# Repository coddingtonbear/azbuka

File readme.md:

# Azbuka: Morse Code USB Keyboard

*Note*: This is directly derived from [@mitxela](https://github.com/mitxela)'s
[Morse USB Keyboard Mk II](https://mitxela.com/projects/morse_code_usb_keyboard_mk_ii);
this varies from his design only in that it includes minor hardware
changes and slightly altered software.  If you were interested in this
project, you will probably also enjoy his
[other projects](https://mitxela.com/projects/hardware) -- check them out!

## Fuse Settings:

* `lfuse`: `0xe1`
* `hfuse`: `0xdd`
* `efuse`: `0xfe`

And, to set those fuses, a command something like:

```
avrdude -U lfuse:w:0xe1:m -U hfuse:w:0xdd:m -U efuse:w:0xfe:m -c arduino -p attiny85 -F -P /dev/cu.usbserial-ADAPHONEX -b 19200
```

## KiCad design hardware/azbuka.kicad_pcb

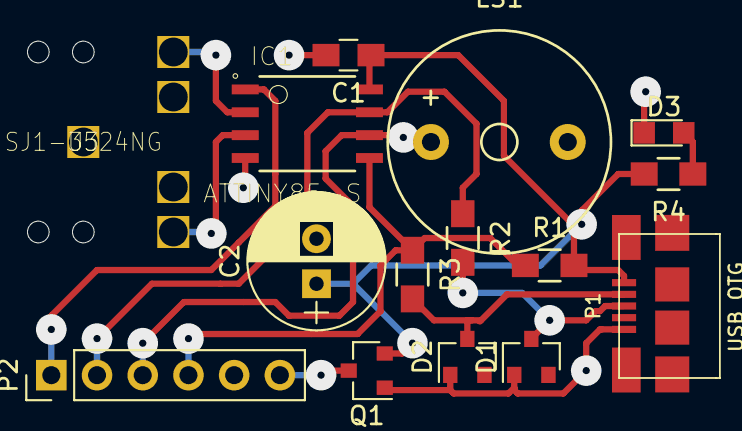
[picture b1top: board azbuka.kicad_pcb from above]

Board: 2 copper layers, 15 parts (0 on the bottom side), 12 nets.

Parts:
C1: 0.1u; C_0805_HandSoldering
C2: 33u; CP_Radial_D7.5mm_P2.50mm
D1, D2: 3.6; D_SOT-23_ANK
D3: LED; LED_0805
IC1: ATTINY85-S; SOIC127P798X216-8N
LS1: Speaker; Buzzer_12x9.5RM7.6
P1: USB_OTG; MICRO-B_USB-INVERTED
P2: CONN_01X06; Pin_Header_Straight_1x06_Pitch2.54mm
Q1: MOSFET_P_CH; MOSFET-SOT-23
R1: 2.2k; R_0805_HandSoldering
R2, R3: 47; R_0805_HandSoldering
R4: R_Small; R_0805_HandSoldering
U3: SJ1-3524NG; PIN-4_MODIFIED_NO_HOLES

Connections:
+5V: C1.1, C2.1, IC1.8, P1.1, Q1.S, R1.2, R4.2
DAH: IC1.2, U3.3
DIT: IC1.3, U3.2
GND: C1.2, C2.2, D1.2, D2.2, D3.1, IC1.4, LS1.2, P1.5, P2.5, Q1.G, U3.1
MISO: IC1.6, LS1.1, P2.3
MOSI: IC1.5, P2.4, R1.1, R3.1
unnamed: D1.1, P1.3, R2.2
unnamed: D2.1, P1.2, R3.2
unnamed: D3.2, R4.1
unnamed: P2.6, Q1.D
RESET: IC1.1, P2.1
SCK: IC1.7, P2.2, R2.1

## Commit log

2017-02-06 And so it begins...
2017-02-07 Updating board file to include USB's required series resistors, 1.5k pullup; fixed ATTINY85 footprint; minor layout changes.
2017-02-07 Minor alterations.
2017-02-07 Copying-in V-USB source & source from https://mitxela.com/projects/morse_code_usb_keyboard_mk_ii
2017-02-07 Moving 'software' folder to 'firmware' folder.
2017-02-10 Updating schematics and masks.
2017-02-10 Adding fuse settings.
2017-02-10 Updating docs.
2017-02-11 Preparing board version 2.0 (swapping TXB0102 for two 3.6v zeners)
2017-02-11 Minor alterations to 2.0 to make it slightly less difficult to assemble.
2017-02-13 Hardware revision 2.1.
2017-02-13 Minor schematic correction for 2.1.
2017-02-14 Updating photo.
2017-02-20 Adding plotted schematic.
2017-06-16 Version 3 completed.
2017-06-16 Updating USB device name.
